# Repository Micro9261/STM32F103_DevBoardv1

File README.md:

First fully developed boards in KiCad that gives opportunity to use all GPIOS by using 2.54mm pins connector.
USB-C with 5V to 3V converter onboard for power supply with led indication.
External crystal oscillator with resistor and capacitor selected accordingly to STM32 design specification.
User button & led and reset button onboard.
Additional analog filter, created by using 100mH coil and 100pF capacitor.

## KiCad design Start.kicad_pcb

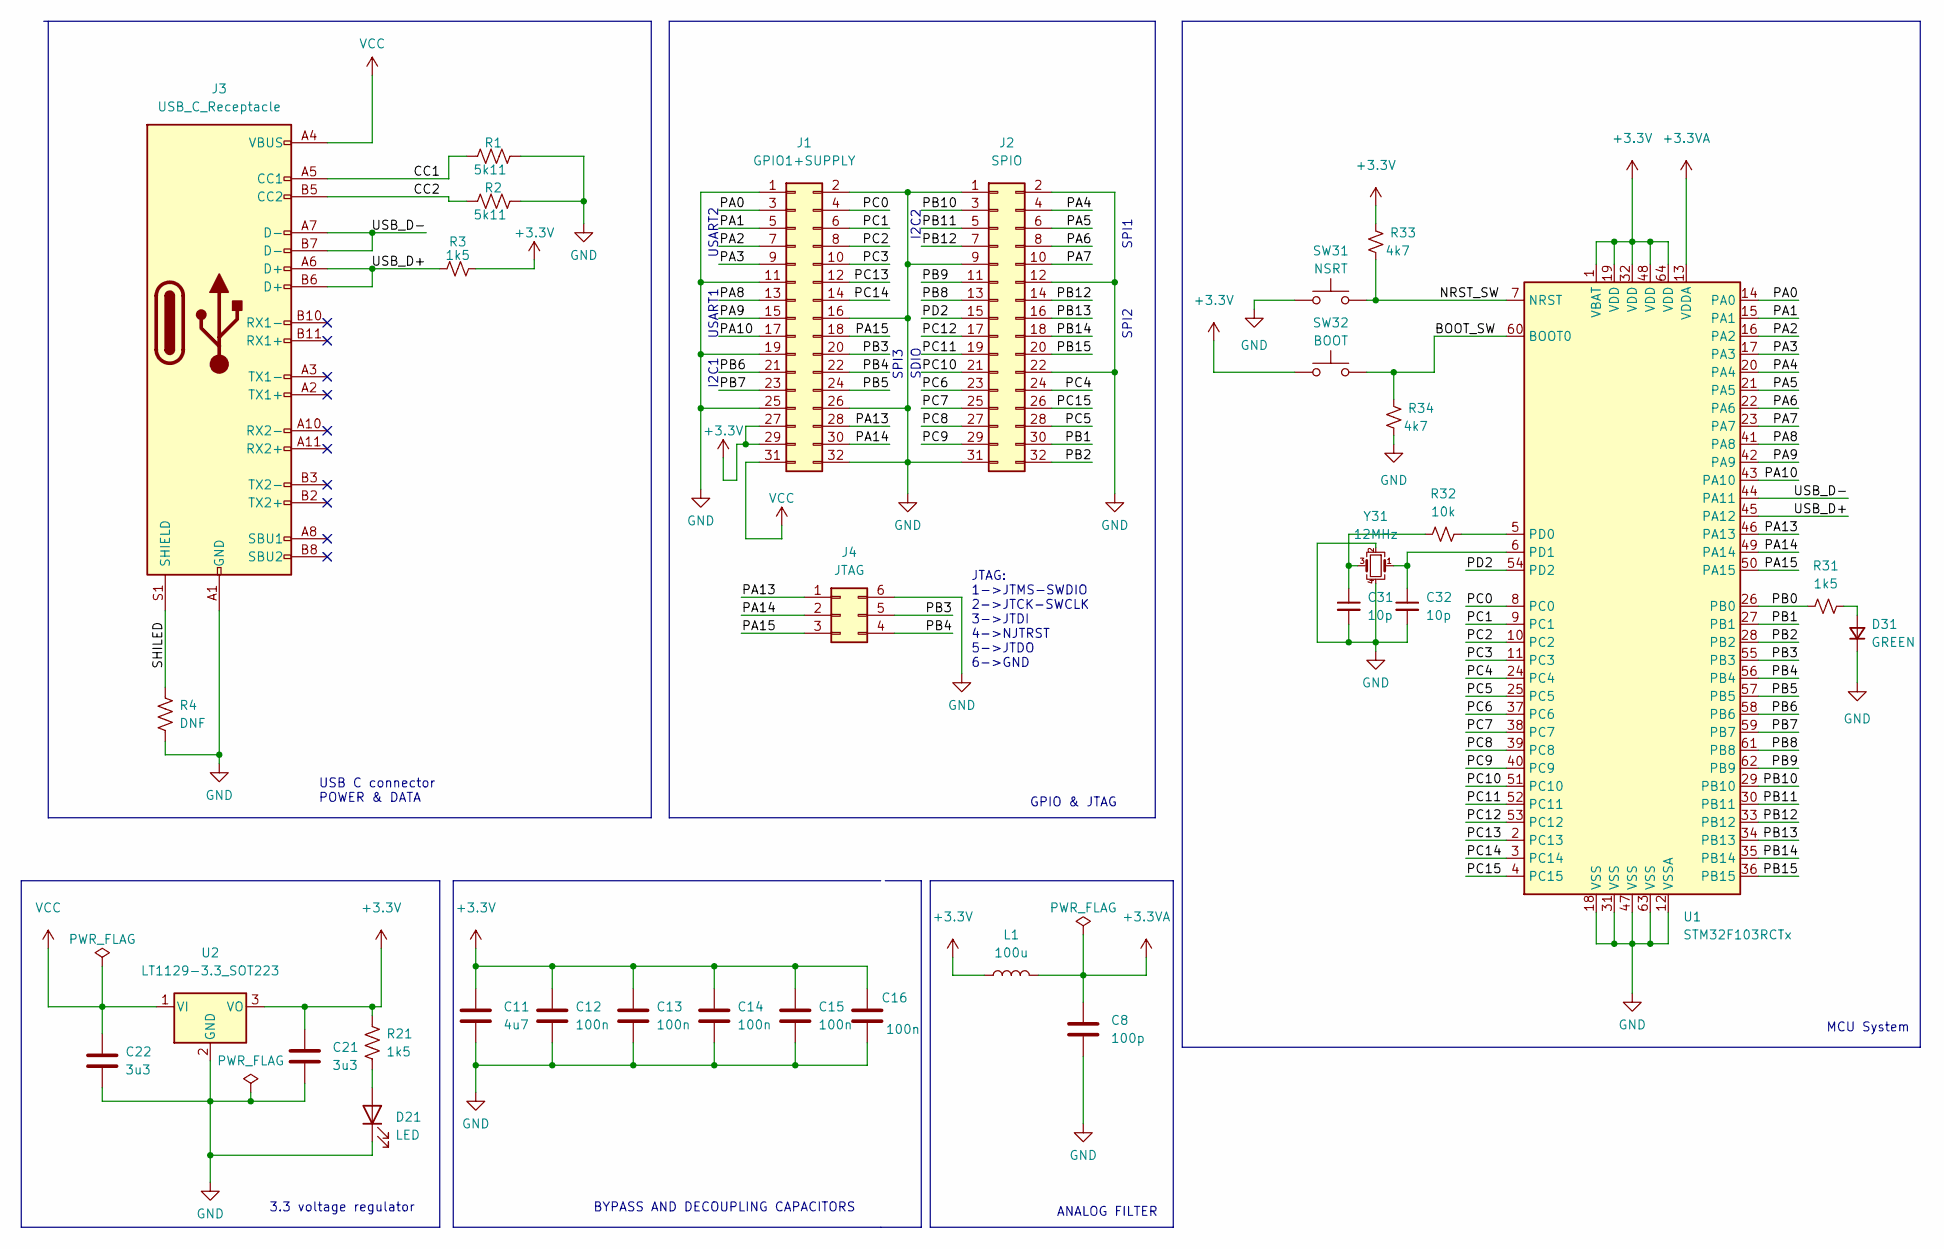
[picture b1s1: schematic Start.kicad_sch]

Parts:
C8: 100p; C_0402_1005Metric
C11: 4u7; C_0603_1608Metric
C12, C13, C14, C15, C16: 100n; C_0402_1005Metric
C21, C22: 3u3; C_0603_1608Metric
C31, C32: 10p; C_0402_1005Metric
D21: LED; D_0603_1608Metric
D31: GREEN; D_0603_1608Metric
J1: GPIO1+SUPPLY; PinHeader_2x16_P2.54mm_Vertical
J2: SPIO; PinHeader_2x16_P2.54mm_Vertical
J3: USB_C_Receptacle; USB_C_China
J4: JTAG; PinHeader_2x03_P2.54mm_Vertical
L1: 100u; L_0603_1608Metric
R1, R2: 5k11; R_0603_1608Metric
R3, R21, R31: 1k5; R_0603_1608Metric
R4: DNF; R_0603_1608Metric
R32: 10k; R_0603_1608Metric
R33, R34: 4k7; R_0603_1608Metric
SW31: NSRT; 3x4x2mm Switch Tactile
SW32: BOOT; 3x4x2mm Switch Tactile
U1: STM32F103RCTx; LQFP-64_10x10mm_P0.5mm
U2: LT1129-3.3_SOT223; SOT-223-3_TabPin2
Y31: 12MHz; Crystal_SMD_EuroQuartz_MT-4Pin_3.2x2.5mm

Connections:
+3.3V: C11.1, C12.1, C13.1, C14.1, C15.1, C16.1, C21.1, J1.27, J1.29, L1.1, R3.2, R21.1, R33.2, SW32.1, U1.1 (VBAT), U1.19 (VDD), U1.32 (VDD), U1.48 (VDD), U1.64 (VDD), U2.3 (VO)
+3.3VA: C8.1, L1.2, U1.13 (VDDA)
/BOOT_SW: R34.2, SW32.2, U1.60 (BOOT0)
/CC1: J3.A5 (CC1), R1.1
/CC2: J3.B5 (CC2), R2.1
/NRST_SW: R33.1, SW31.2, U1.7 (NRST)
/PA0: J1.3, U1.14 (PA0)
/PA1: J1.5, U1.15 (PA1)
/PA2: J1.7, U1.16 (PA2)
/PA3: J1.9, U1.17 (PA3)
/PA4: J2.4, U1.20 (PA4)
/PA5: J2.6, U1.21 (PA5)
/PA6: J2.8, U1.22 (PA6)
/PA7: J2.10, U1.23 (PA7)
/PA8: J1.13, U1.41 (PA8)
/PA9: J1.15, U1.42 (PA9)
/PA10: J1.17, U1.43 (PA10)
/PA13: J1.28, J4.1, U1.46 (PA13)
/PA14: J1.30, J4.2, U1.49 (PA14)
/PA15: J1.18, J4.3, U1.50 (PA15)
/PB0: R31.1, U1.26 (PB0)
/PB1: J2.30, U1.27 (PB1)
/PB2: J2.32, U1.28 (PB2)
/PB3: J1.20, J4.5, U1.55 (PB3)
/PB4: J1.22, J4.4, U1.56 (PB4)
/PB5: J1.24, U1.57 (PB5)
/PB6: J1.21, U1.58 (PB6)
/PB7: J1.23, U1.59 (PB7)
/PB8: J2.13, U1.61 (PB8)
/PB9: J2.11, U1.62 (PB9)
/PB10: J2.3, U1.29 (PB10)
/PB11: J2.5, U1.30 (PB11)
/PB12: J2.7, J2.14, U1.33 (PB12)
/PB13: J2.16, U1.34 (PB13)
/PB14: J2.18, U1.35 (PB14)
/PB15: J2.20, U1.36 (PB15)
/PC0: J1.4, U1.8 (PC0)
/PC1: J1.6, U1.9 (PC1)
/PC2: J1.8, U1.10 (PC2)
/PC3: J1.10, U1.11 (PC3)
/PC4: J2.24, U1.24 (PC4)
/PC5: J2.28, U1.25 (PC5)
/PC6: J2.23, U1.37 (PC6)
/PC7: J2.25, U1.38 (PC7)
/PC8: J2.27, U1.39 (PC8)
/PC9: J2.29, U1.40 (PC9)
/PC10: J2.21, U1.51 (PC10)
/PC11: J2.19, U1.52 (PC11)
/PC12: J2.17, U1.53 (PC12)
/PC13: J1.12, U1.2 (PC13)
/PC14: J1.14, U1.3 (PC14)
/PC15: J2.26, U1.4 (PC15)
/PD2: J2.15, U1.54 (PD2)
/SHILED: J3.S1 (SHIELD), R4.1
/USB_D+: J3.A6 (D+), J3.B6 (D+), R3.1, U1.45 (PA12)
/USB_D-: J3.A7 (D-), J3.B7 (D-), U1.44 (PA11)
GND: C8.2, C11.2, C12.2, C13.2, C14.2, C15.2, C16.2, C21.2, C22.2, C31.2, C32.2, D21.1 (K), D31.1 (K), J1.1, J1.2, J1.11, J1.16, J1.19, J1.25, J1.26, J1.32, J2.1, J2.2, J2.9, J2.12, J2.22, J2.31, J3.A1 (GND), J3.A12 (GND), J3.B1 (GND), J3.B12 (GND), J4.6, R1.2, R2.2, R4.2, R34.1, SW31.1, U1.12 (VSSA), U1.18 (VSS), U1.31 (VSS), U1.47 (VSS), U1.63 (VSS), U2.2 (GND), Y31.2, Y31.4
unnamed: C31.1, R32.1, Y31.3
unnamed: C32.1, U1.6 (PD1), Y31.1
unnamed: D21.2 (A), R21.2
unnamed: D31.2 (A), R31.2
unnamed: R32.2, U1.5 (PD0)
VCC: C22.1, J1.31, J3.A4 (VBUS), J3.A9 (VBUS), J3.B4 (VBUS), J3.B9 (VBUS), U2.1 (VI)

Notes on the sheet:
I2C1
SPI2
ANALOG FILTER
SDIO
USART2
3.3 voltage regulator
SPI1
USART1
BYPASS AND DECOUPLING CAPACITORS
MCU System
SPI3
USB C connector POWER & DATA
JTAG: 1->JTMS-SWDIO 2->JTCK-SWCLK 3->JTDI 4->NJTRST 5->JTDO 6->GND
I2C2
GPIO & JTAG

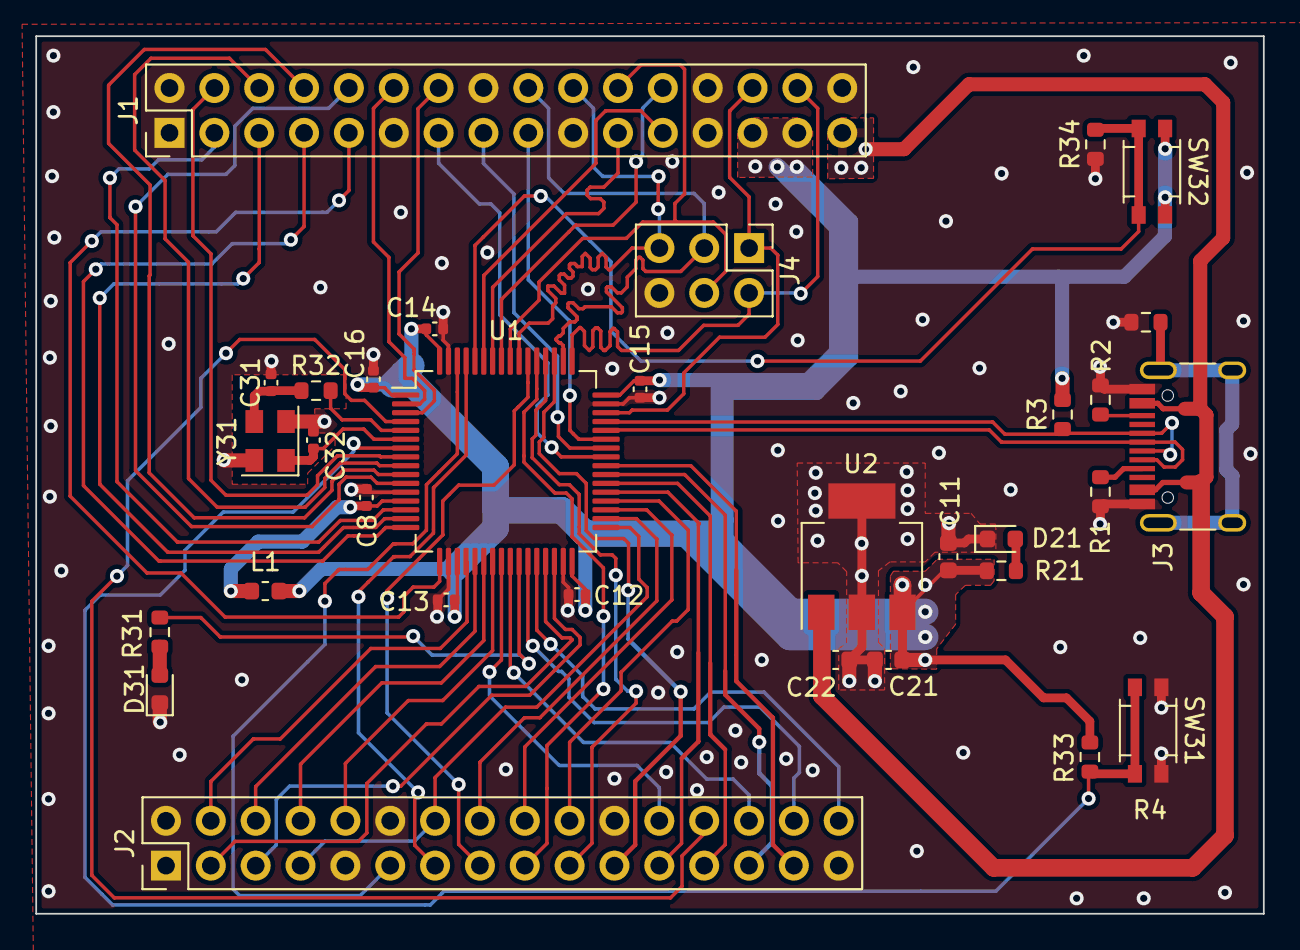
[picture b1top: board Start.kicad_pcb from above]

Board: 2 copper layers, 69.5 x 49.7 mm, 32 parts (0 on the bottom side), 63 nets.
